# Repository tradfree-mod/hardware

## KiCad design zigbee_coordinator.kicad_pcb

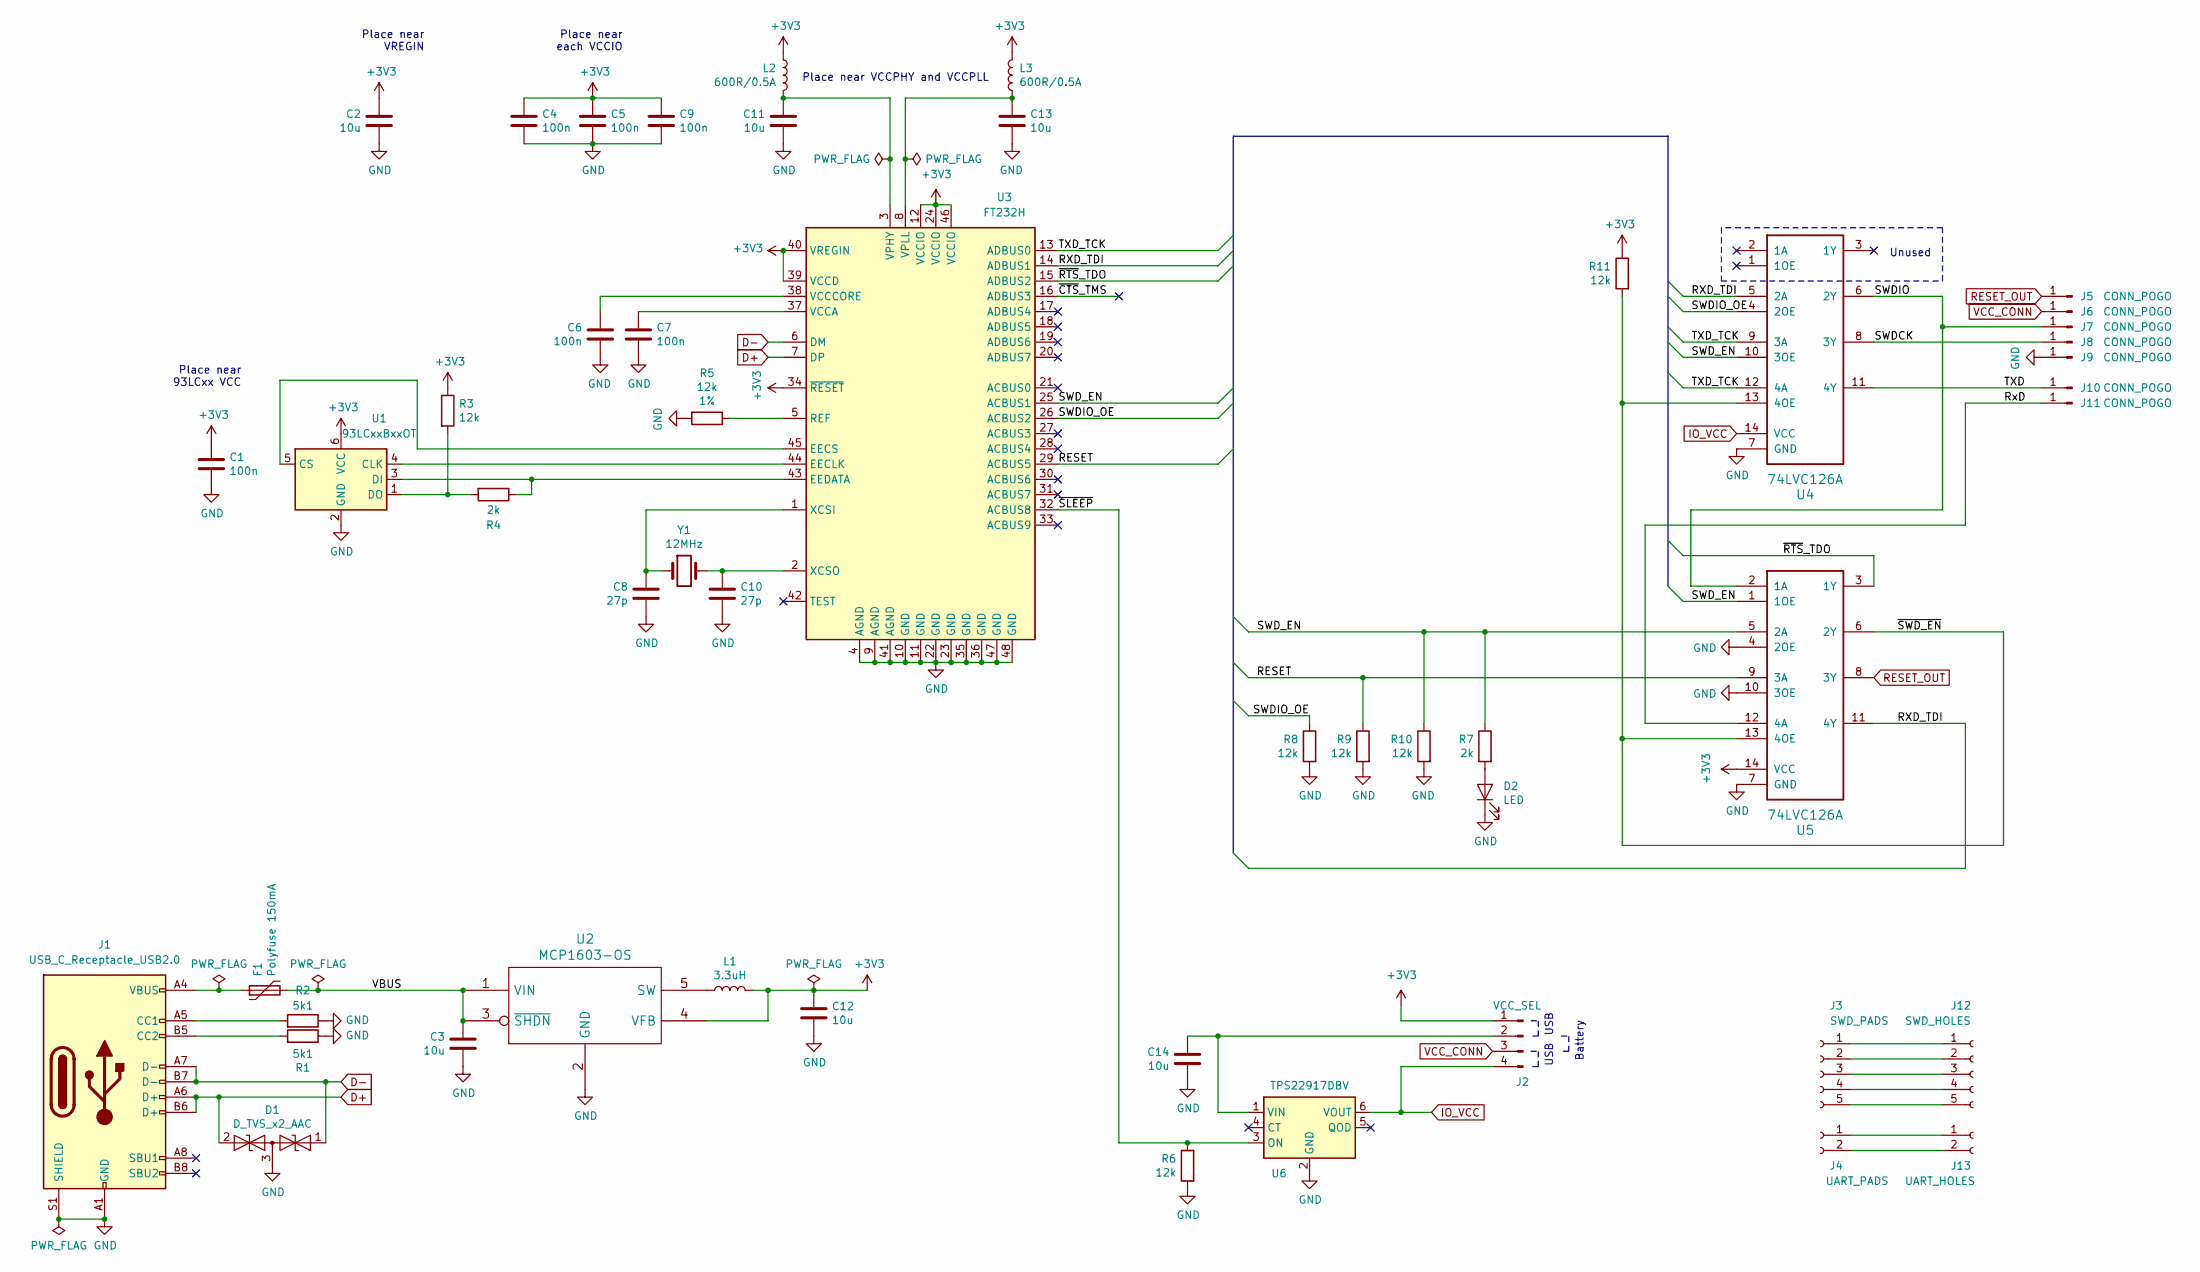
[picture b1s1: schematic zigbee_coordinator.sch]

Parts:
C1, C4, C5, C6, C7, C9: 100n; C_0805_2012Metric
C2, C3, C11, C12, C13, C14: 10u; C_0805_2012Metric
C8, C10: 27p; C_0805_2012Metric
D1: D_TVS_x2_AAC; SOT-23
D2: LED; LED_0805_2012Metric
F1: Polyfuse 150mA; Fuse_0805_2012Metric
J1: USB_C_Receptacle_USB2.0; USB_C_Receptacle_GCT_USB4085
J2: VCC_SEL; PinHeader_1x04_P1.27mm_Horizontal
J3: SWD_PADS; SWD_pads
J4: UART_PADS; UART_pads
J5, J6, J7, J8, J9, J10, J11: CONN_POGO; pogopin
J12: SWD_HOLES; SWD_holes
J13: UART_HOLES; UART_holes
L1: 3.3uH; L_0805_2012Metric
L2, L3: 600R/0.5A; L_0805_2012Metric
R1, R2: 5k1; R_0805_2012Metric
R3, R5, R6, R8, R9, R10, R11: 12k; R_0805_2012Metric
R4, R7: 2k; R_0805_2012Metric
U1: 93LCxxBxxOT; SOT-23-6
U2: MCP1603-OS; SOT-23-5
U3: FT232H; LQFP-48_7x7mm_P0.5mm
U4, U5: 74LVC126A; TSSOP-14_4.4x5mm_P0.65mm
U6: TPS22917DBV; SOT-23-6
Y1: 12MHz; Crystal_SMD_0603-2Pin_6.0x3.5mm

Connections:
+3V3: C1.1, C2.1, C4.1, C5.1, C9.1, C12.1, J2.1, L1.2, L2.2, L3.2, R3.1, R11.1, U1.6 (VCC), U2.4 (VFB), U3.12 (VCCIO), U3.24 (VCCIO), U3.34 (~RESET), U3.39 (VCCD), U3.40 (VREGIN), U3.46 (VCCIO), U5.14 (VCC)
/RESET: R9.1, U3.29 (ACBUS5), U5.9 (3A)
/RXD_TDI: U3.14 (ADBUS1), U4.5 (2A), U5.11 (4Y)
/RxD: J11.1, U5.12 (4A)
/SWDCK: J8.1, U4.8 (3Y)
/SWDIO: J7.1, U4.6 (2Y), U5.2 (1A)
/SWDIO_OE: R8.1, U3.26 (ACBUS2), U4.4 (2OE)
/SWD_EN: R7.1, R10.1, U3.25 (ACBUS1), U4.10 (3OE), U5.1 (1OE), U5.5 (2A)
/TXD: J10.1, U4.11 (4Y)
/TXD_TCK: U3.13 (ADBUS0), U4.9 (3A), U4.12 (4A)
/VBUS: C3.1, F1.2, U2.1 (VIN), U2.3 (~SHDN~)
/~CTS~_TMS: U3.16 (ADBUS3)
/~RTS~_TDO: U3.15 (ADBUS2), U5.3 (1Y)
/~SLEEP: R6.1, U3.32 (ACBUS8), U6.3 (ON)
/~SWD_EN: R11.2, U4.13 (4OE), U5.6 (2Y), U5.13 (4OE)
D+: D1.2 (A2), J1.A6 (D+), J1.B6 (D+), U3.7 (DP)
D-: D1.1 (A1), J1.A7 (D-), J1.B7 (D-), U3.6 (DM)
GND: C1.2, C2.2, C3.2, C4.2, C5.2, C6.2, C7.2, C8.2, C9.2, C10.2, C11.2, C12.2, C13.2, C14.2, D1.3 (common), D2.1 (K), J1.A1 (GND), J1.A12 (GND), J1.B1 (GND), J1.B12 (GND), J1.S1 (SHIELD), J9.1, R1.1, R2.1, R5.2, R6.2, R8.2, R9.2, R10.2, U1.2 (GND), U2.2 (GND), U3.4 (AGND), U3.9 (AGND), U3.10 (GND), U3.11 (GND), U3.22 (GND), U3.23 (GND), U3.35 (GND), U3.36 (GND), U3.41 (AGND), U3.47 (GND), U3.48 (GND), U4.7 (GND), U5.4 (2OE), U5.7 (GND), U5.10 (3OE), U6.2 (GND)
IO_VCC: J2.4, U4.14 (VCC), U6.6 (VOUT)
unnamed: C6.1, U3.38 (VCCCORE)
unnamed: C7.1, U3.37 (VCCA)
unnamed: C8.1, U3.1 (XCSI), Y1.1
unnamed: C10.1, U3.2 (XCSO), Y1.2
unnamed: C11.1, L2.1, U3.3 (VPHY)
unnamed: C13.1, L3.1, U3.8 (VPLL)
unnamed: C14.1, J2.2, U6.1 (VIN)
unnamed: D2.2 (A), R7.2
unnamed: F1.1, J1.A4 (VBUS), J1.A9 (VBUS), J1.B4 (VBUS), J1.B9 (VBUS)
unnamed: J1.A5 (CC1), R2.2
unnamed: J1.B5 (CC2), R1.2
unnamed: J3.1, J12.1
unnamed: J3.2, J12.2
unnamed: J3.3, J12.3
unnamed: J3.4, J12.4
unnamed: J3.5, J12.5
unnamed: J4.1, J13.1
unnamed: J4.2, J13.2
unnamed: L1.1, U2.5 (SW)
unnamed: R3.2, R4.2, U1.1 (DO)
unnamed: R4.1, U1.3 (DI), U3.43 (EEDATA)
unnamed: R5.1, U3.5 (REF)
unnamed: U1.4 (CLK), U3.44 (EECLK)
unnamed: U1.5 (CS), U3.45 (EECS)
RESET_OUT: J5.1, U5.8 (3Y)
VCC_CONN: J2.3, J6.1

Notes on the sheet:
Place near each VCCIO
Place near VREGIN
Place near VCCPHY and VCCPLL
Unused
Place near 93LCxx VCC
Battery
USB

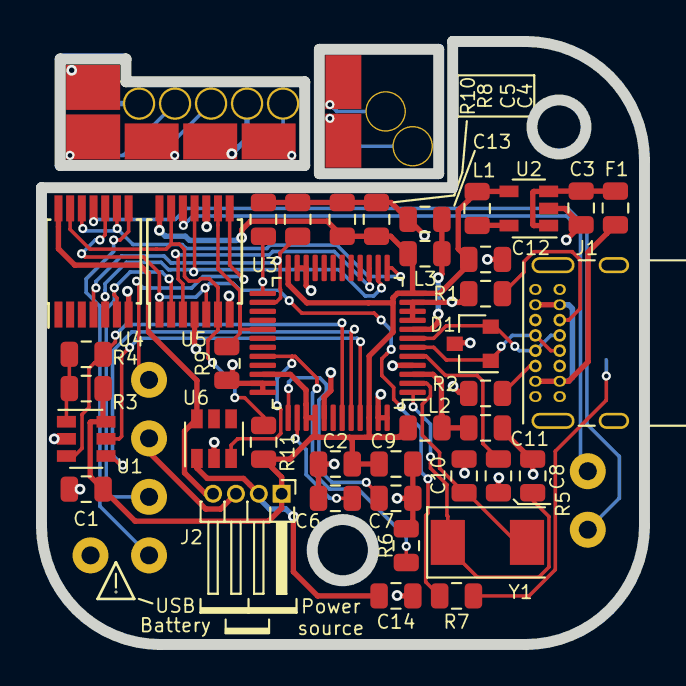
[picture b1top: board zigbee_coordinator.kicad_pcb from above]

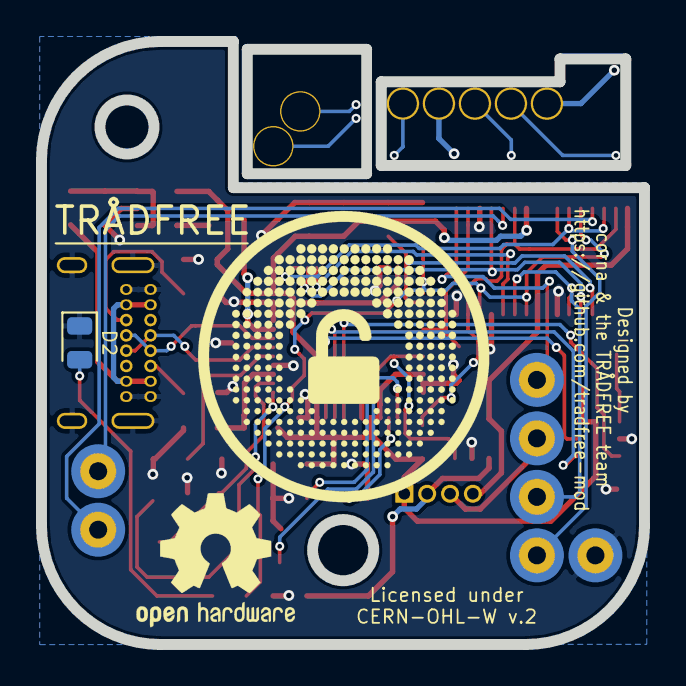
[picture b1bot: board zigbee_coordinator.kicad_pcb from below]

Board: 2 copper layers, 33.5 x 33.5 mm, 51 parts (8 on the bottom side), 44 nets.

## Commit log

2020-02-01 Before second 74LVC126
2020-02-09 First alpha release
2020-03-01 Apply fizzo's fixes
2020-03-02 Replace pogopin 3D model to STEP
    The size scale is wrong, the result should be checked carefully.
2020-03-29 Finalize

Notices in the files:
zigbee_coordinator.kicad_pcb:
Licensed under
CERN-OHL-W v.2
